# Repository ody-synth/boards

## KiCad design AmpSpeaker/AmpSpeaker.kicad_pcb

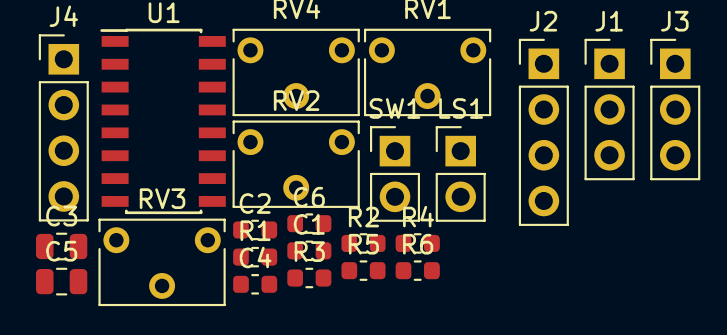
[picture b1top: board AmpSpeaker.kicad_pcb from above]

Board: 2 copper layers, 23 parts (0 on the bottom side), 18 nets, no tracks yet.

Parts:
C1, C2, C4, C6: 1uF; C_0603_1608Metric
C3, C5: 0.47uF; C_0805_2012Metric
J1: L; PinHeader_1x03_P2.54mm_Vertical
J2, J4: LR; PinHeader_1x04_P2.54mm_Vertical
J3: R; PinHeader_1x03_P2.54mm_Vertical
LS1: Speaker; PinHeader_1x02_P2.54mm_Vertical
R1, R2, R5, R6: 10k; R_0603_1608Metric
R3, R4: 500; R_0603_1608Metric
RV1, RV2, RV4: 100k; Potentiometer_Bourns_3266W_Vertical
RV3: 1k; Potentiometer_Bourns_3266W_Vertical
SW1: SW_DIP_x01; PinHeader_1x02_P2.54mm_Vertical
U1: PAM8406; SOIC-16_3.9x9.9mm_P1.27mm

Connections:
-OUT_L: R3.1, U1.3
-OUT_R: R4.2, U1.14
GND: C1.1, C2.1, C4.2, C6.1, RV4.2, U1.2, U1.9, U1.11, U1.15
L: C3.2, R1.1
unnamed: C3.1, U1.7
unnamed: C4.1, U1.8
unnamed: C5.2, U1.10
unnamed: R6.1, RV4.3
unnamed: R5.1, RV4.1
unnamed: LS1.1, SW1.2
unnamed: LS1.2, R3.2, R4.1
unnamed: R1.2, RV1.2
unnamed: R2.2, RV2.2
unnamed: RV3.2, SW1.1
OUT_L: R5.2, RV3.1, U1.1
OUT_R: R6.2, RV3.3, U1.16
R: C5.1, R2.1
VDD: C1.2, C2.2, C6.2, U1.4, U1.5, U1.6, U1.13

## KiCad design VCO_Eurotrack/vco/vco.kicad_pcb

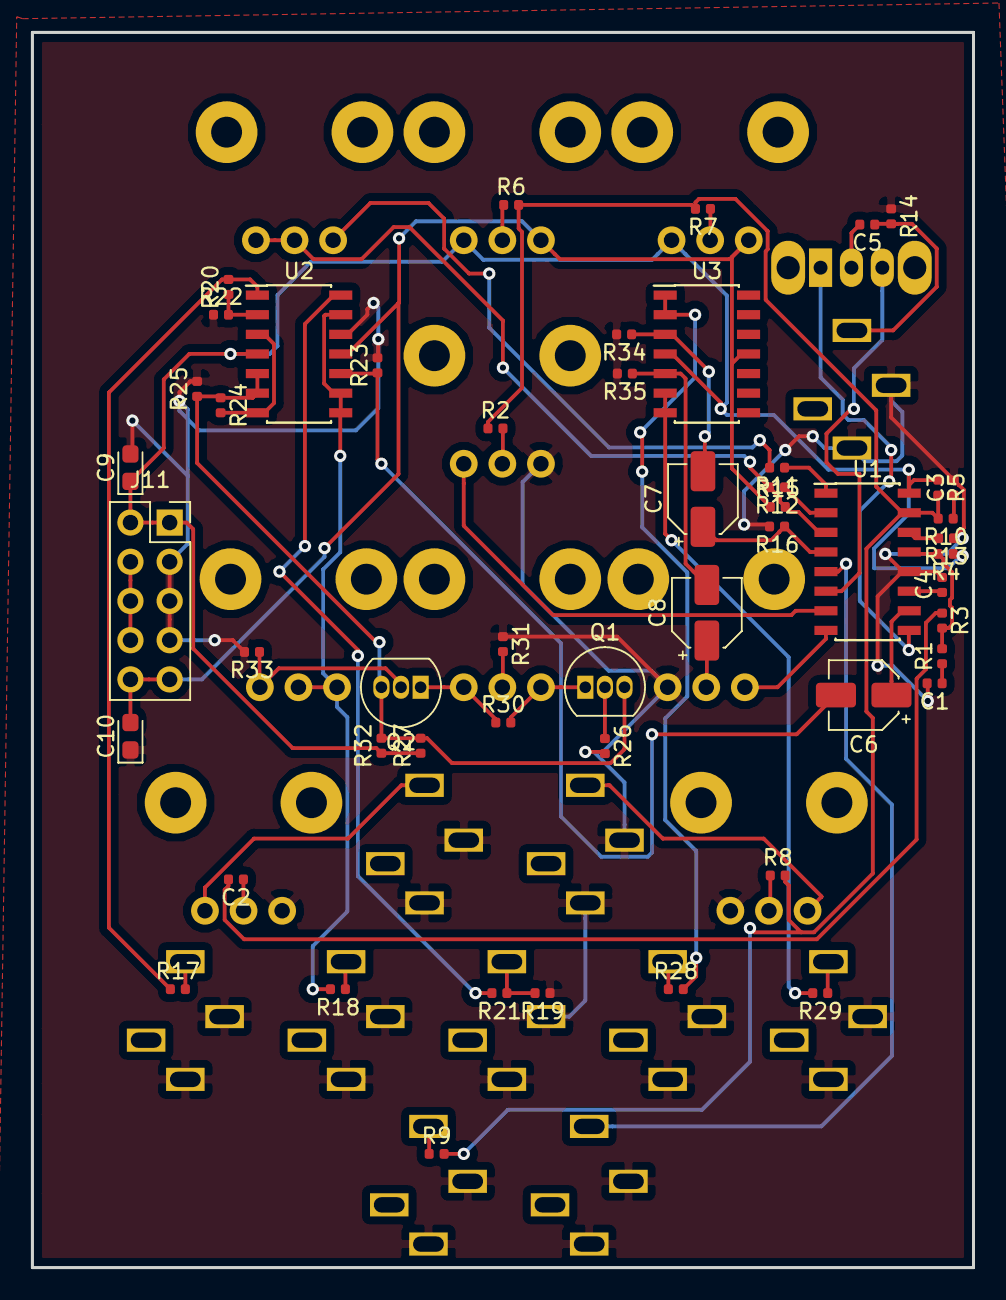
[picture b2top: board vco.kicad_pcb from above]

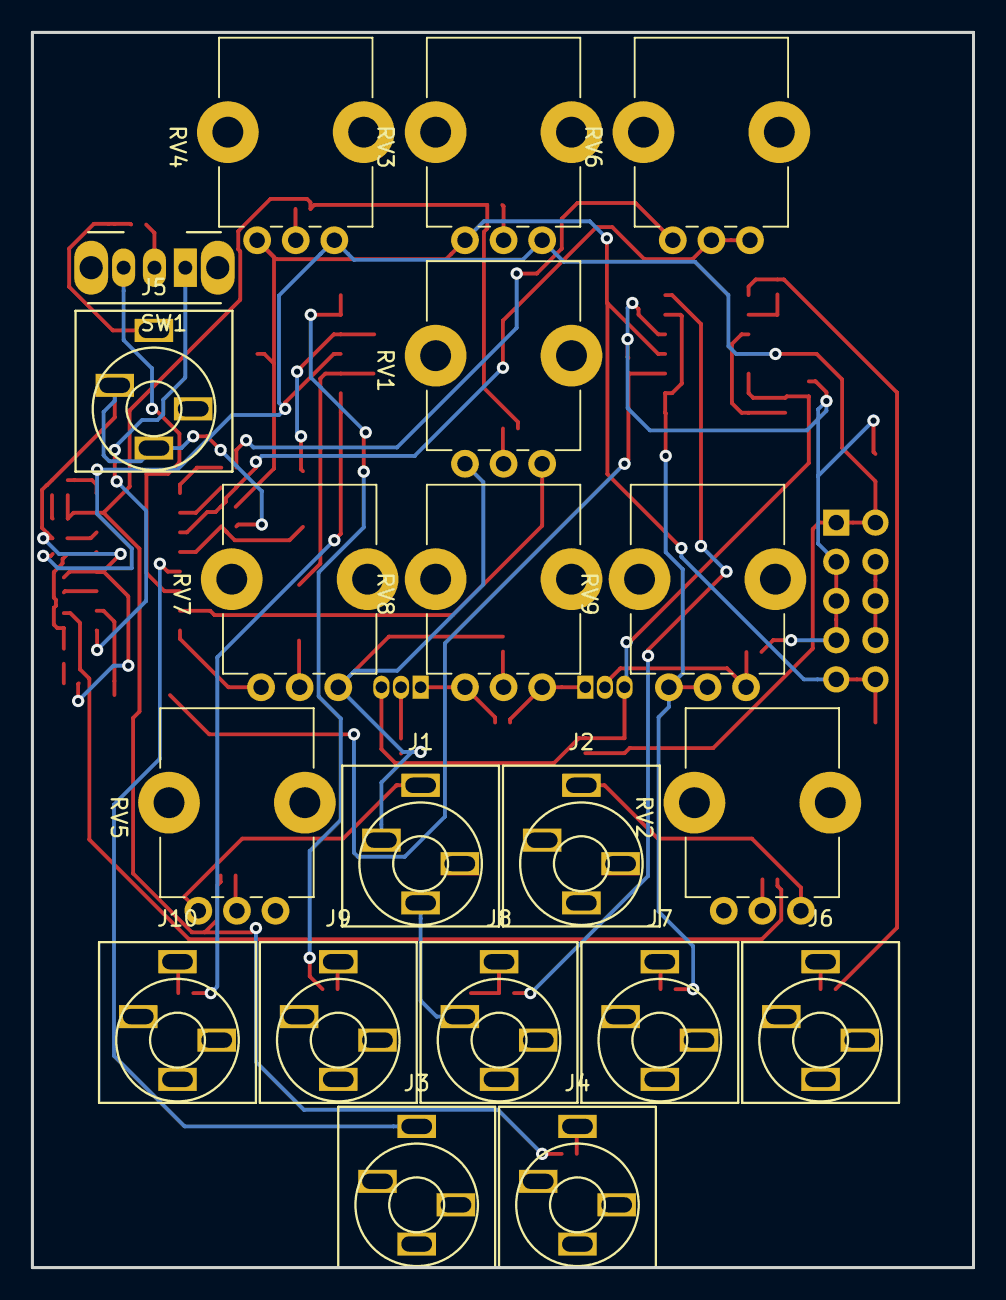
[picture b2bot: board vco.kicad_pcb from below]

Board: 2 copper layers, 61.0 x 80.0 mm, 71 parts (20 on the bottom side), 54 nets.

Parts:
C1, C3: 10nF; C_0402_1005Metric
C2: 100nF; C_0402_1005Metric
C4, C5: 1nF; C_0402_1005Metric
C6, C7, C8: 47uF; CP_Elec_4x5.4
C9, C10: 10uF; CP_EIA-2012-12_Kemet-R
J1: EXP_FM; jack_audio
J2: LIN_FM; jack_audio
J3: PWM_IN; jack_audio
J4: CV 1V/OCT; jack_audio
J5: SYNC_IN; jack_audio
J6: SINE; jack_audio
J7: TRI; jack_audio
J8: SQUARE; jack_audio
J9: PULSE; jack_audio
J10: SAW; jack_audio
J11: Conn_02x05_Odd_Even; PinSocket_2x05_P2.54mm_Vertical
Q1, Q2: 2N3904; TO-92_Inline
R1, R10, R26, R33: 470; R_0402_1005Metric
R2, R3: 1M; R_0402_1005Metric
R4: 1.5M; R_0402_1005Metric
R5: 360K; R_0402_1005Metric
R6: 1.2M; R_0402_1005Metric
R7: 5.6M; R_0402_1005Metric
R8, R9, R14: 100K; R_0402_1005Metric
R11: 24K; R_0402_1005Metric
R12: 5.6K; R_0402_1005Metric
R13: 1.8k; R_0402_1005Metric
R15: 820; R_0402_1005Metric
R16: 51K; R_0402_1005Metric
R17, R18, R28, R29: 1K; R_0402_1005Metric
R19: 82K; R_0402_1005Metric
R20, R22, R23, R27, R32, R34, R35: 10K; R_0402_1005Metric
R21: 15K; R_0402_1005Metric
R24, R25: 22K; R_0402_1005Metric
R30: 220; R_0402_1005Metric
R31: 68K; R_0402_1005Metric
RV1: 20K; Potentiometer_Bourns_PTV09A-1_Single_Vertical
RV2, RV3, RV4, RV5: 100k; Potentiometer_Bourns_PTV09A-1_Single_Vertical
RV6, RV7: 10K; Potentiometer_Bourns_PTV09A-1_Single_Vertical
RV8: 50K; Potentiometer_Bourns_PTV09A-1_Single_Vertical
RV9: 100K; Potentiometer_Bourns_PTV09A-1_Single_Vertical
SW1: SW_SPDT; SW_CuK_OS102011MA1QN1_SPDT_Angled
U1: AS3340; SOIC-16_3.9x9.9mm_P1.27mm
U2, U3: TL074; SOIC-14_3.9x8.7mm_P1.27mm

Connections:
+12V: C9.1, J11.1, J11.2, R4.1, R5.1, R27.1, R32.1, RV3.1, RV4.1, U1.16, U2.4, U3.4
-12V: C10.2, J11.9, J11.10, R15.1, RV3.3, RV4.3, U2.11, U3.11
GND: C1.2, C3.2, C4.2, C9.2, C10.1, J1.G, J1.S, J2.G, J2.S, J3.G, J3.S, J4.G, J4.S, J5.G, J5.S, J6.G, J6.S, J7.G, J7.S, J8.G, J8.S, J9.G, J9.S, J10.G, J10.S, J11.3, J11.5, J11.7, R13.1, R14.1, R16.2, R19.1, R22.1, R23.2, R25.2, R26.2, R31.1, R33.2, R34.2, R35.2, RV1.3, RV2.3, RV5.1, RV7.1, U1.12, U2.12
unnamed: C1.1, R1.1
unnamed: C2.1, RV2.2
unnamed: C2.2, R3.1
unnamed: C3.1, R10.1
unnamed: C4.1, U1.11
unnamed: C5.1, J5.T, R14.2
unnamed: C5.2, SW1.2
unnamed: C6.2, R23.1, U2.10
unnamed: C7.2, R34.1, U3.3
unnamed: C8.2, R35.1, U3.5
unnamed: J1.T, RV5.3
unnamed: J2.T, RV2.1
unnamed: J4.T, R9.1
unnamed: J6.T, R17.2
unnamed: J7.T, R18.1
unnamed: J8.T, R19.2, R21.1
unnamed: J9.T, R28.1
unnamed: J10.T, R29.1
unnamed: J11.4, J11.6, J11.8
unnamed: Q1.1, R30.2, RV8.3
unnamed: Q1.2, R26.1
unnamed: Q1.3, Q2.3, R24.1, R25.1, R27.2, R32.2, U2.5, U2.6
unnamed: Q2.1, R30.1, RV8.1
unnamed: Q2.2, R33.1, RV9.1
unnamed: R2.2, RV1.2
unnamed: R6.1, RV3.2
unnamed: R7.1, RV4.2
unnamed: R8.1, RV5.2
unnamed: R11.1, U1.1
unnamed: R11.2, RV6.3
unnamed: R12.1, U1.2
unnamed: R13.2, U1.14
unnamed: R17.1, R20.2, U2.1
unnamed: R20.1, R22.2, U2.2
unnamed: R21.2, U2.14
unnamed: R24.2, U2.3, U2.7
unnamed: R28.2, U3.1, U3.2
unnamed: R29.2, U3.6, U3.7
unnamed: R31.2, RV8.2
unnamed: RV7.3, U1.8
PULSE: C7.1, R16.1, U1.4
REE: R12.2, R15.2, RV6.1, RV6.2, U1.3
SAW: C8.1, RV7.2
TRIANGLE: C6.1, U1.10
TRI_OUT: R18.2, RV9.2, RV9.3, U2.8, U2.9, U2.13
VFCI: R2.1, R5.2, R6.2, R7.2, R8.2, R9.2, R10.2, U1.15
VHFT: RV1.1, U1.7
VHSI: SW1.3, U1.6
VLFI: R1.2, R3.2, R4.2, U1.13
VPWM: J3.T, U1.5
VSSI: SW1.1, U1.9

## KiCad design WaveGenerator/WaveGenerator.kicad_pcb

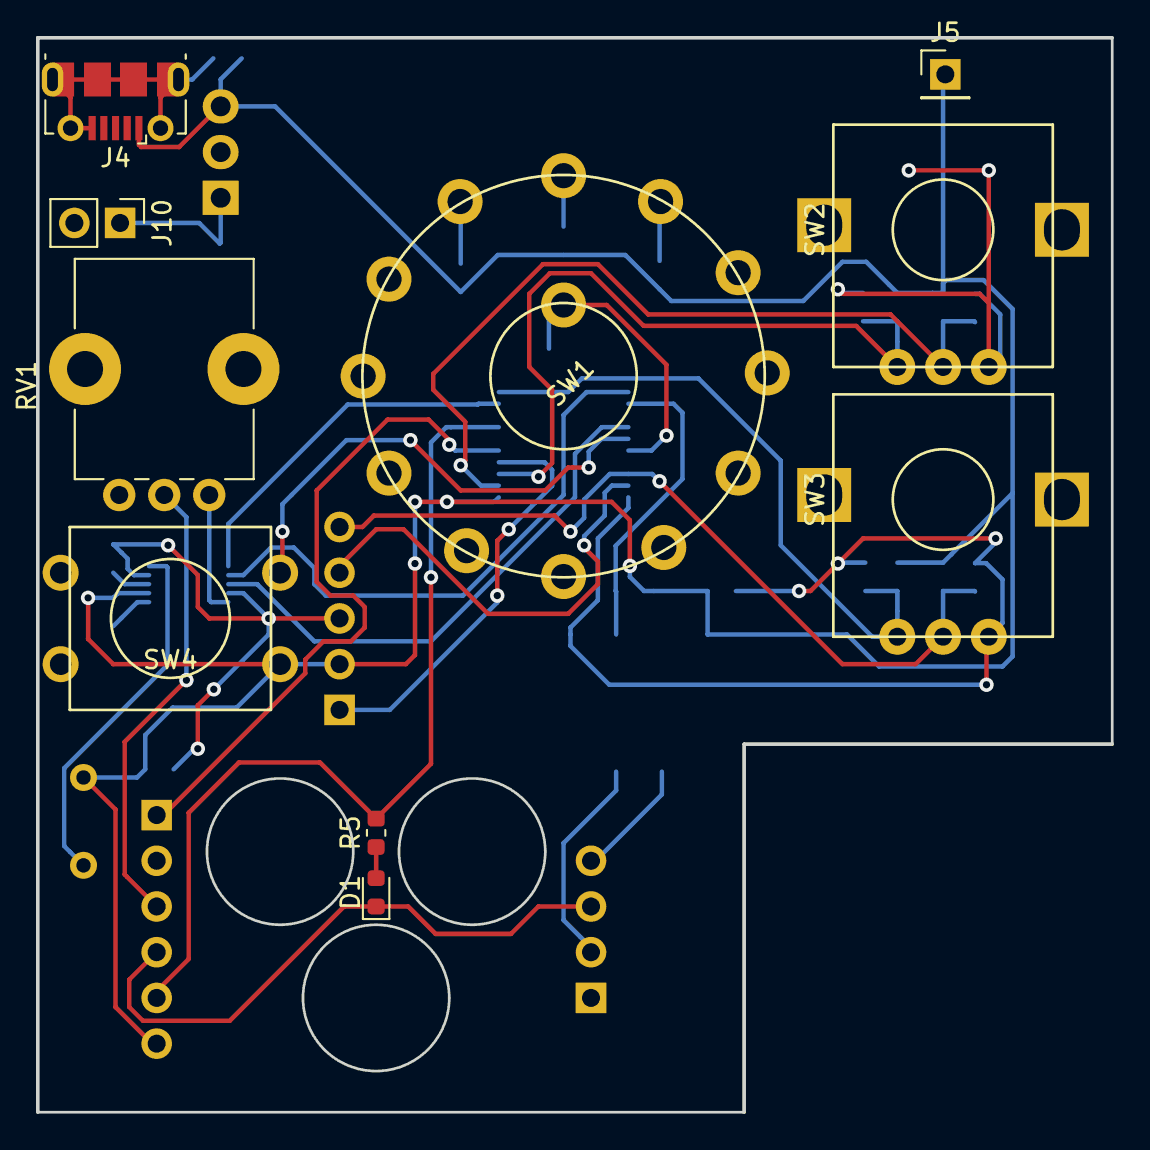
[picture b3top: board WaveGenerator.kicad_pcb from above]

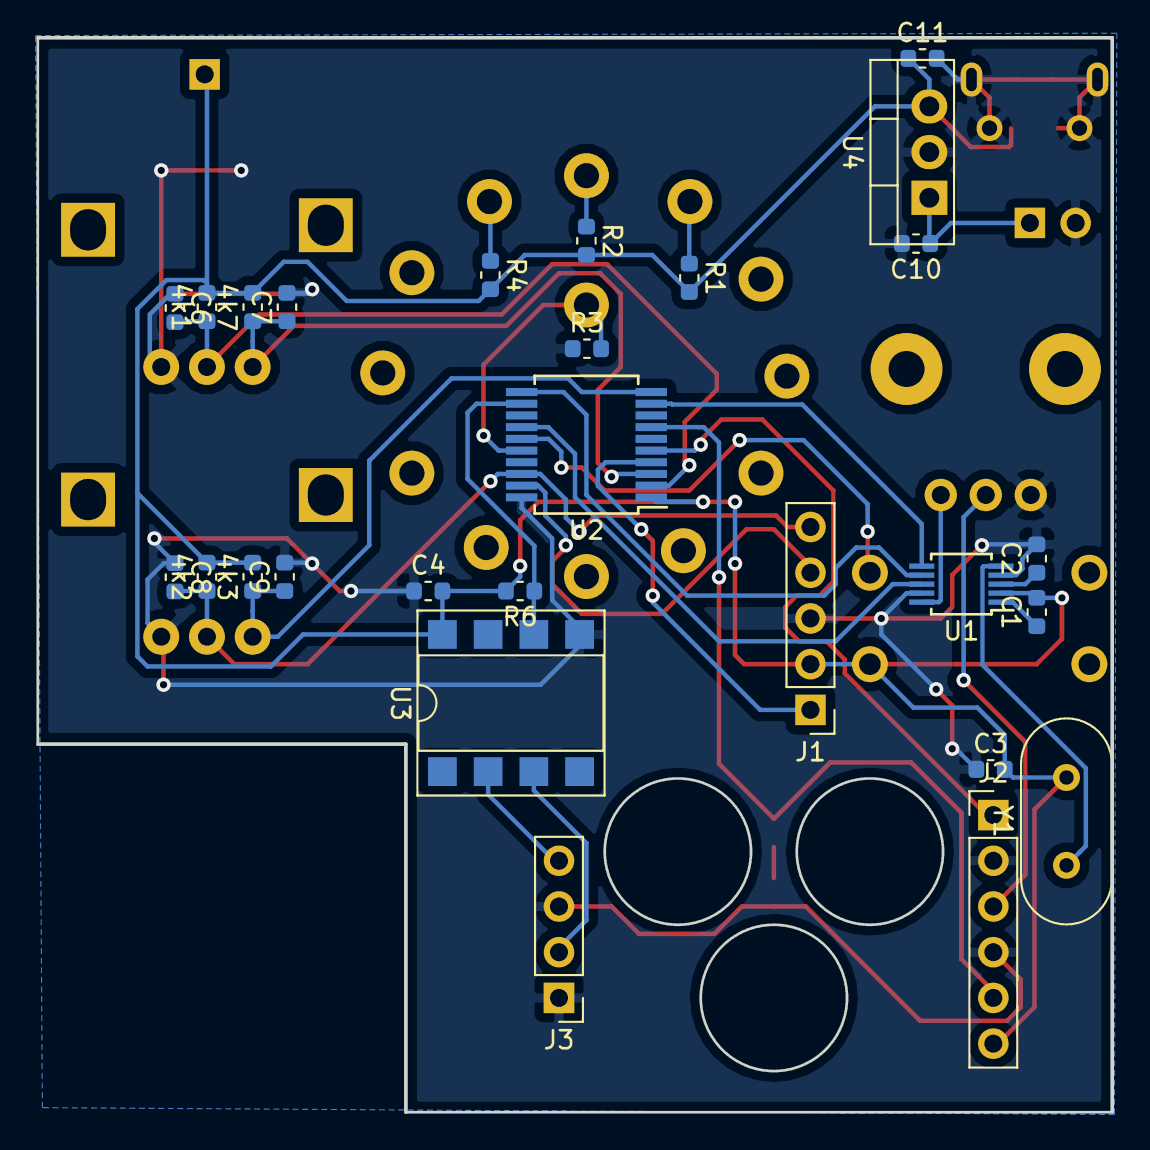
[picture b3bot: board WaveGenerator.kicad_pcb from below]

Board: 2 copper layers, 59.7 x 59.7 mm, 37 parts (27 on the bottom side), 28 nets.

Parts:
4k1, 4k2, 4k3, 4k7: R; R_0603_1608Metric
C1: 10nF; C_0603_1608Metric
C2, C3, C6, C7, C8, C9: 100nF; C_0603_1608Metric
C4, C11: 0.1uF; C_0603_1608Metric
C10: 0.33uF; C_0603_1608Metric
D1: LED; LED_0603_1608Metric
J1: Conn_01x05; PinHeader_1x05_P2.54mm_Vertical
J2: Conn_01x06; PinHeader_1x06_P2.54mm_Vertical
J3: Conn_01x04; PinHeader_1x04_P2.54mm_Vertical
J4: USB_OTG; USB_Micro-B_Molex-105017-0001
J5: VDD; PinHeader_1x01_P2.54mm_Vertical
J10: Conn_01x02; PinHeader_1x02_P2.54mm_Vertical
R1: 10; R_0603_1608Metric
R2, R3, R6: 1k; R_0603_1608Metric
R4: 10k; R_0603_1608Metric
R5: 100; R_0603_1608Metric
RV1: 20k; Potentiometer_Bourns_PTV09A-1_Single_Vertical
SW1: MODE; rotary_12
SW2: D; Bourns-PEC12R-N
SW3: F; Bourns-PEC12R-N
SW4: TRIG; PUSH_BUTTON
U1: AD9833; MSOP-10_3x3mm_P0.5mm
U2: PIC16F1459-ISS; SSOP-20_5.3x7.2mm_P0.65mm
U3: 6N137; DIP-8_W7.62mm_SMDSocket_SmallPads
U4: LM7805_TO220; TO-220-3_Vertical
Y1: 4MHz; Crystal_HC49-4H_Vertical

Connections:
A1: 4k7.1, C7.1, SW2.A, U2.3
A2: 4k3.1, C9.1, SW3.A, U2.10
B1: 4k1.1, C6.2, SW2.B, U2.2
B2: 4k2.1, C8.2, J1.5, SW3.B, U2.18
BAT+: C10.1, J10.1, U4.1
BAT-: C2.2, C3.1, C4.1, C6.1, C7.2, C8.1, C9.2, C10.2, C11.2, D1.1, J1.3, J2.2, J2.4, J3.1, J3.3, J4.5, J4.6, J10.2, R3.1, RV1.3, SW2.C, SW3.C, U1.4, U1.9, U2.20, U3.5, U4.2
D1: J3.4, U3.2
D2: J3.2, U3.3
FSYNC: U1.8, U2.14
MCLR: J1.1, U2.4
MIDI-IN: R6.1, U2.12, U3.6
unnamed: C1.1, U1.1
unnamed: C2.1, U1.3
unnamed: D1.2, R5.1
unnamed: R1.1, SW1.1
unnamed: R2.1, SW1.2
unnamed: R3.2, SW1.13, U2.16
unnamed: R4.1, SW1.3
unnamed: SW4.3, U2.15
unnamed: U1.5, Y1.1
PGD: J1.4, U2.19
PWM: J2.1, U2.5
SCK: U1.7, U2.11
SDO: U1.6, U2.9
TRIGGER: J2.5, R5.2, U2.7
VDD: 4k1.2, 4k2.2, 4k3.2, 4k7.2, C1.2, C3.2, C4.2, C11.1, J1.2, J2.6, J4.1, J5.1, R1.2, R2.2, R4.2, R6.2, SW4.1, U1.2, U2.1, U3.8, U4.3, Y1.2
VOUT: RV1.1, U1.10
VOUT_: J2.3, RV1.2

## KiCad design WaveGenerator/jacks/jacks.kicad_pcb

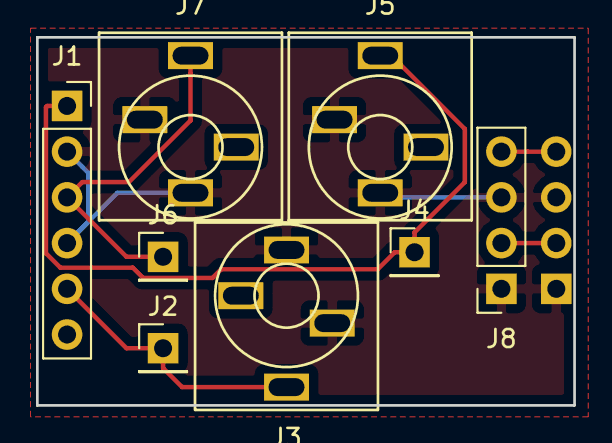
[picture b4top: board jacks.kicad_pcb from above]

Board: 2 copper layers, 29.8 x 20.4 mm, 9 parts (1 on the bottom side), 6 nets.

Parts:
J1: Conn_01x06; PinSocket_1x06_P2.54mm_Vertical
J2: TRIGGER; PinHeader_1x01_P2.54mm_Vertical
J3: TRIG; jack_audio
J4: PWM; PinHeader_1x01_P2.54mm_Vertical
J5: PWM; jack_audio
J6: VOUT; PinHeader_1x01_P2.54mm_Vertical
J7: VOUT; jack_audio
J8: Conn_01x04; PinSocket_1x04_P2.54mm_Vertical
J9: Conn_01x04; PinHeader_1x04_P2.54mm_Horizontal

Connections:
D1: J8.4, J9.4
D2: J8.2, J9.2
GND: J1.2, J1.4, J3.G, J3.S, J5.G, J5.S, J7.G, J7.S, J8.1, J8.3, J9.1, J9.3
PWM: J1.1, J4.1, J5.T
TRIGGER: J1.5, J2.1, J3.T
VOUT_: J1.3, J6.1, J7.T

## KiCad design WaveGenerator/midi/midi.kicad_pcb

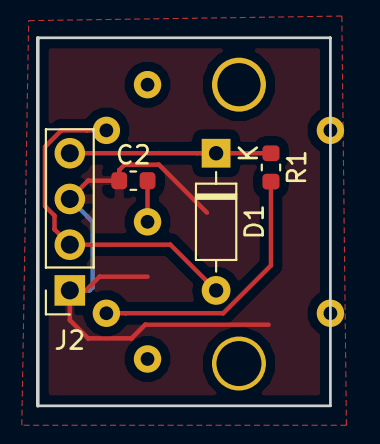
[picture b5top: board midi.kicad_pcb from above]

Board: 2 copper layers, 16.3 x 20.4 mm, 5 parts (1 on the bottom side), 5 nets.

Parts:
C2: 10nF; C_0603_1608Metric
D1: 1N4148; D_DO-35_SOD27_P7.62mm_Horizontal
J1: MIDI IN; MIDI_IN
J2: Conn_01x04; PinSocket_1x04_P2.54mm_Vertical
R1: 220; R_0603_1608Metric

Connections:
D1: D1.1, J2.4, R1.1
D2: D1.2, J1.5, J2.2
GND: C2.1, J2.1, J2.3
unnamed: C2.2, J1.2
unnamed: J1.4, R1.2
